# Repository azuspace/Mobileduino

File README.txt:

Mobileduino is an RC Car to Robot Conversion kit. For more info please visit the following links:

Site:
http://mobileduino.com/

Forum/Group:
http://techjango.com/group/mobileduino

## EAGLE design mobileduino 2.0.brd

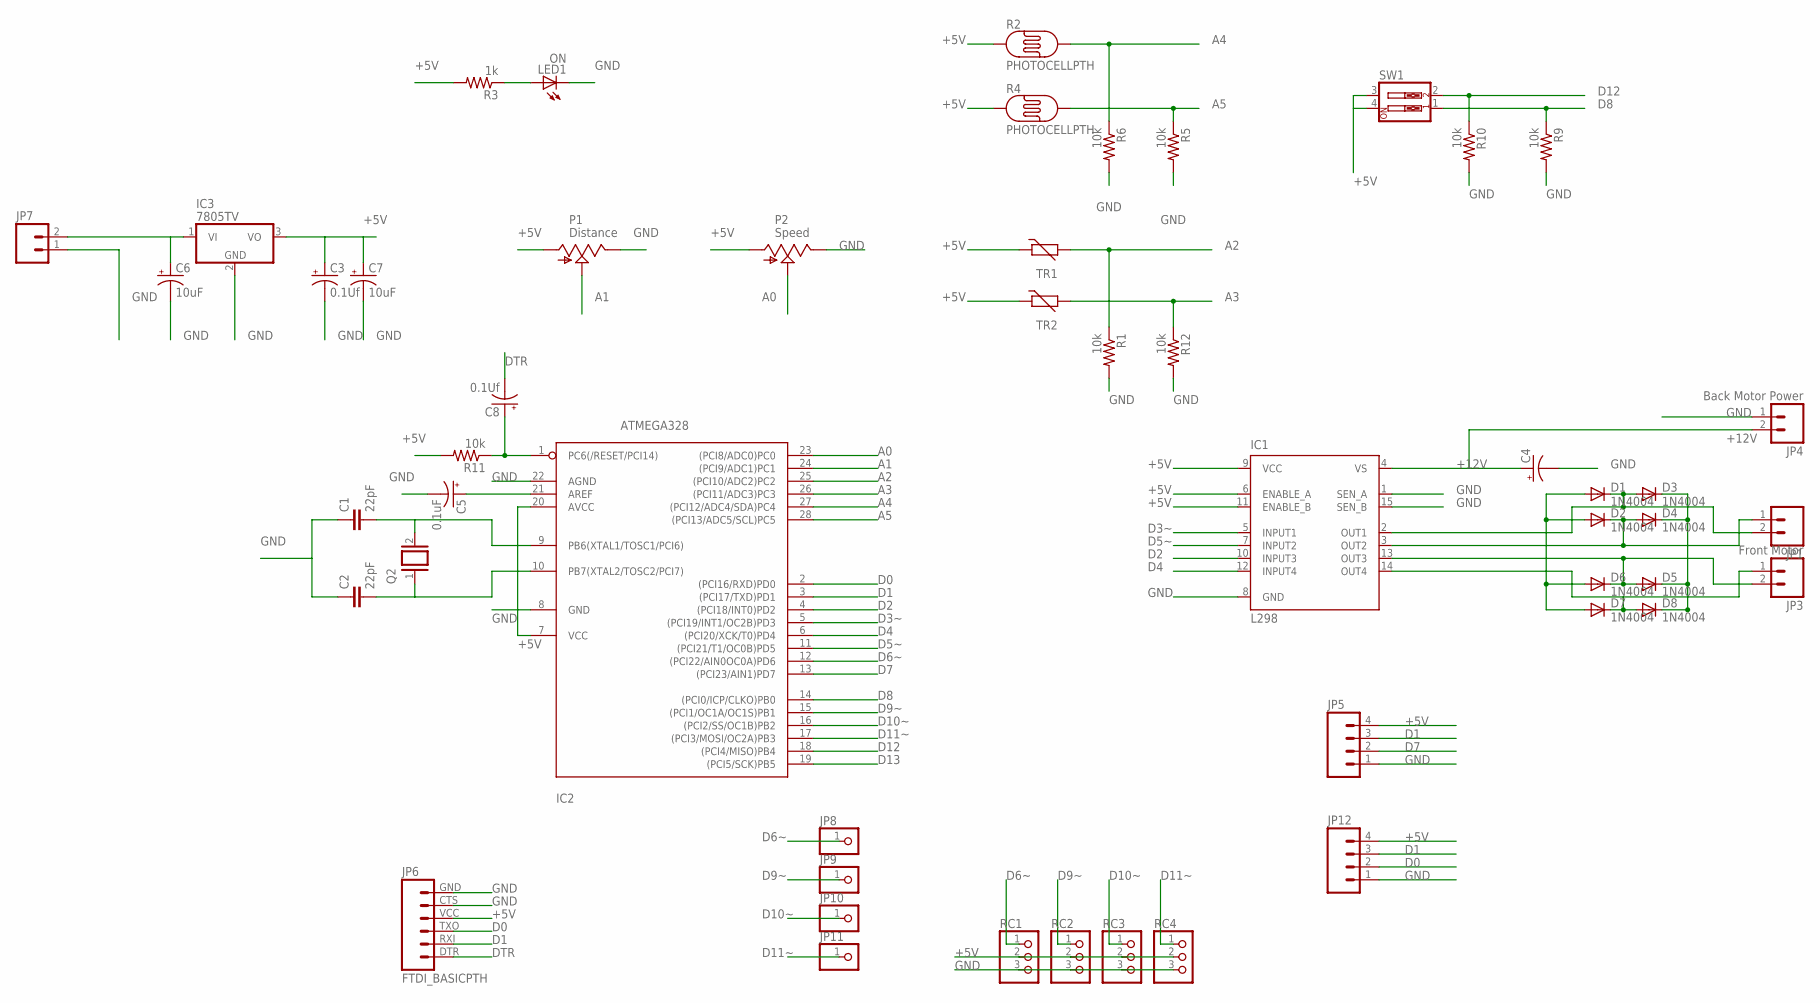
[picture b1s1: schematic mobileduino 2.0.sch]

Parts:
C1, C2: 22pF; C5B2.5
C3, C8: 0.1Uf; TT2D5
C4: CPOL-USTT2D5; TT2D5
C5: 0.1uF; TT2D5
C6, C7: 10uF; TT2D5
D1, D2, D3, D4, D5, D6, D7, D8: 1N4004; DO41-10
IC1: L298; MULTIWATT-15
IC2: ATMEGA328; DIL28-3
IC3: 7805TV; TO220V
JP1, JP7: M025MM; SCREWTERMINAL-5MM-2
JP3: Front Motor; SCREWTERMINAL-5MM-2
JP4: Back Motor Power; SCREWTERMINAL-5MM-2
JP5, JP12: M04PTH; 1X04
JP6: FTDI_BASICPTH; FTDI_BASIC
JP8, JP9, JP10, JP11: PINHD-1X1; 1X01
LED1: ON; LED3MM
P1: Distance; CA6V
P2: Speed; CA6V
Q2: XTAL/S; QS
R1, R5, R6, R9, R10, R11, R12: 10k; 0204V
R2, R4: PHOTOCELLPTH; PHOTOCELL
R3: 1k; 0204V
RC1, RC2, RC3, RC4: PINHD-1X3; 1X03
SW1: SW_DIP-2; EDG-02
TR1, TR2: THERMISTOR_R-2,5; RS-2,5

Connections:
+5V: C3.+, C7.+, IC1.6 (ENABLE_A), IC1.9 (VCC), IC1.11 (ENABLE_B), IC2.7 (VCC), IC2.20 (AVCC), IC3.3 (VO), JP5.4, JP6.VCC (4), JP12.4, P1.A, P2.A, R2.1, R3.2, R4.1, R11.2, RC1.2, RC2.2, RC3.2, RC4.2, SW1.3, SW1.4, TR1.1, TR2.1
+12V: C4.+, IC1.4 (VS), JP4.2
A0: IC2.23 ((PCI8/ADC0)PC0), P2.S
A1: IC2.24 ((PCI9/ADC1)PC1), P1.S
A2: IC2.25 ((PCI10/ADC2)PC2), R1.1, TR1.2
A3: IC2.26 ((PCI11/ADC3)PC3), R12.1, TR2.2
A4: IC2.27 ((PCI12/ADC4/SDA)PC4), R2.2, R6.1
A5: IC2.28 ((PCI13/ADC5/SCL)PC5), R4.2, R5.1
D0: IC2.2 ((PCI16/RXD)PD0), JP6.TXO (3), JP12.2
D1: IC2.3 ((PCI17/TXD)PD1), JP5.3, JP6.RXI (2), JP12.3
D2: IC1.10 (INPUT3), IC2.4 ((PCI18/INT0)PD2)
D3~: IC1.5 (INPUT1), IC2.5 ((PCI19/INT1/OC2B)PD3)
D4: IC1.12 (INPUT4), IC2.6 ((PCI20/XCK/T0)PD4)
D5~: IC1.7 (INPUT2), IC2.11 ((PCI21/T1/OC0B)PD5)
D6~: IC2.12 ((PCI22/AIN0OC0A)PD6), JP8.1, RC1.1
D7: IC2.13 ((PCI23/AIN1)PD7), JP5.2
D8: IC2.14 ((PCI0/ICP/CLKO)PB0), R9.1, SW1.1
D9~: IC2.15 ((PCI1/OC1A/OC1S)PB1), JP9.1, RC2.1
D10~: IC2.16 ((PCI2/SS/OC1B)PB2), JP10.1, RC3.1
D11~: IC2.17 ((PCI3/MOSI/OC2A)PB3), JP11.1, RC4.1
D12: IC2.18 ((PCI4/MISO)PB4), R10.1, SW1.2
D13: IC2.19 ((PCI5/SCK)PB5)
DTR: C8.-, JP6.DTR (1)
GND: C1.1, C2.1, C3.-, C4.-, C5.-, C6.-, C7.-, IC1.1 (SEN_A), IC1.8 (GND), IC1.15 (SEN_B), IC2.8 (GND), IC2.22 (AGND), IC3.2 (GND), JP4.1, JP5.1, JP6.CTS (5), JP6.GND (6), JP7.1, JP12.1, LED1.K (C), P1.E, P2.E, R1.2, R5.2, R6.2, R9.2, R10.2, R12.2, RC1.3, RC2.3, RC3.3, RC4.3
unnamed: D1.C, D3.A, IC1.2 (OUT1), JP1.2
unnamed: C8.+, IC2.1 (PC6(/RESET/PCI14)), R11.1
unnamed: C2.2, IC2.10 (PB7(XTAL2/TOSC2/PCI7)), Q2.1
unnamed: D2.C, D4.A, IC1.3 (OUT2), JP1.1
unnamed: D5.A, D6.C, IC1.13 (OUT3), JP3.2
unnamed: D7.C, D8.A, IC1.14 (OUT4), JP3.1
unnamed: C6.+, IC3.1 (VI), JP7.2
unnamed: C1.2, IC2.9 (PB6(XTAL1/TOSC1/PCI6)), Q2.2
unnamed: C5.+, IC2.21 (AREF)
unnamed: D3.C, D4.C, D5.C, D8.C
unnamed: D1.A, D2.A, D6.A, D7.A
unnamed: LED1.A, R3.1

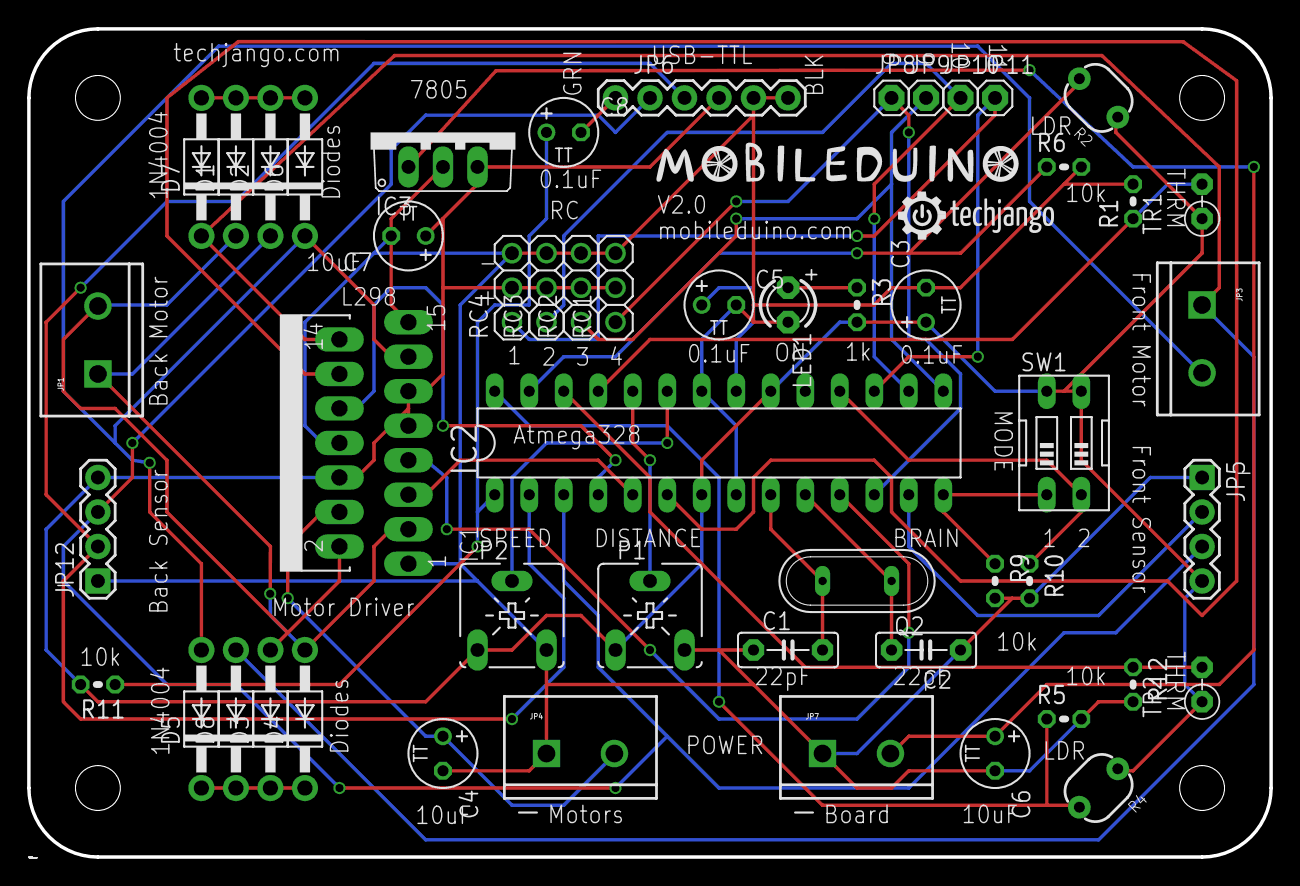
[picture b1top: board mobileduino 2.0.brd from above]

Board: 2 copper layers, 91.4 x 61.0 mm, 55 parts (0 on the bottom side), 35 nets.

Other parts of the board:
U$1, U$2, U$3, U$4: STAND-OFF

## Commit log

2013-02-25 Mobileduino V2.0
2013-02-25 Readme updated
2013-02-25 gerbers
2013-03-07 added mobileduino 1.0
2013-03-07 deleted extraneous git files
2013-03-07 some renaming for ver 2
2013-05-07 Mobileduino example code and Ultrasonic library
    Paste the ultrasonic library within the 'libraries' folder of your
    arduino folder to use example code

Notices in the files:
parts and their libraries:
SparkFun-Connectors: Licensing: CC v3.0 Share-Alike You are welcome to use this library for commercial purposes.
